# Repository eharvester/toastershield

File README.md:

# **toastershield**

An SMT reflow oven shield for the Arduino Uno.

## 1. Software
 
 The following steps were tested in Linux (Ubuntu).
 
### Set the following environment variables

`PATH_TO_ARDUINO_IDE = /path/to/your/arduinoIDE`

`ARDUINO_IDE_VER = 1.6.X`  (depending on your version)

`GITHUB_MIRROR = /path/to/your/github/mirror` (optional, local github mirror otherwise https://github.com is used per default)

### Connect Arduino Uno via USB cable

Make sure you have write permissions to `/dev/ttyUSB0` and execute the following commands:

`$make`

`$make upload`

If the shield is attached to the Arduino Uno board, you should hear a beep  and see something on the display.

## 2. Hardware

**_WARNING - DANGER - HIGH VOLTAGE - ELECTRIC SHOCK HAZARD - EXPERTS ONLY
(shield, heater, fan and transformer are connected to 120VAC)_**

### Parts List:

- toaster oven, to be converted (for use on 120VAC)
- Arduino Uno board
- toastershield PCB (see Eagle files and parts list)
- transformer PCB (see Eagle files and parts list)
- SH1106 OLED module
- 2 pushbuttons
- 1 LED,
- 2 wafer connectors (4 pin)
- some ribbon cable (to connect the OLED module and the switches+LED with wafer connectors)
- power cable with ground / 20 A
- power cable feedthrough coupler
- K-type thermocouple wire pair (about 50cm)
- some cable (AWG 16 for heater, AWG 24 for fan and 12VAC supply)
- 6.3mm crimp terminal spade connectors (female, insulated)
- ring tongue crimp terminals (for grounding)
- hardware for mounting boards and grounding
- fiberglass cloth (for thermal insulation)
- silicone glue

PCBs can be made with the [toner transfer method](http://www.instructables.com/id/Cheap-and-Easy-Toner-Transfer-for-PCB-Making) easily (single layer). All goes inside the oven (original buttons, switches, timers, bell aso. are stripped out). Make sure that there is sufficient air ventilation in order to keep the temperature around the boards and cables below 70C (a cooling fan might be necessary). Some thermal insulation on the outside of the oven compartment is necessary (treat fiberglass cloth with silicon glue on the cutting lines before cutting). Cut out an opening for the USB port, preferably on the front (so you can easily update the firmware and optionally monitor and control the oven from a computer).  Drill a hole into the oven compartment wall and feed the thermocouple wire pair through it and seal the hole with silicone glue later (after everything is working and tested). 

**_WARNING - DANGER - HIGH VOLTAGE - ELECTRIC SHOCK HAZARD - EXPERTS ONLY
(shield, heater, fan and transformer are connected to 120VAC)_**

## 3. To Do
- menu for adjusting temperature/time (at the moment fixed for PbSn solder) via pushbuttons
- interface for Processing
- Processing GUI  

***
## Pictures:

Picture 1: Assembled shield top.
***

Picture 2: Assembled shield bottom.
***

Picture 3: Modified power connection, plug replaced by screw terminals.
***

Picture 4: Wired shield sitting on Uno board.
***

Picture 5: Wired transformer board.
***

Picture 6: Complete wiring.
***

Picture 7: Wiring of front panel.
***

Pincture 8: Front panel.

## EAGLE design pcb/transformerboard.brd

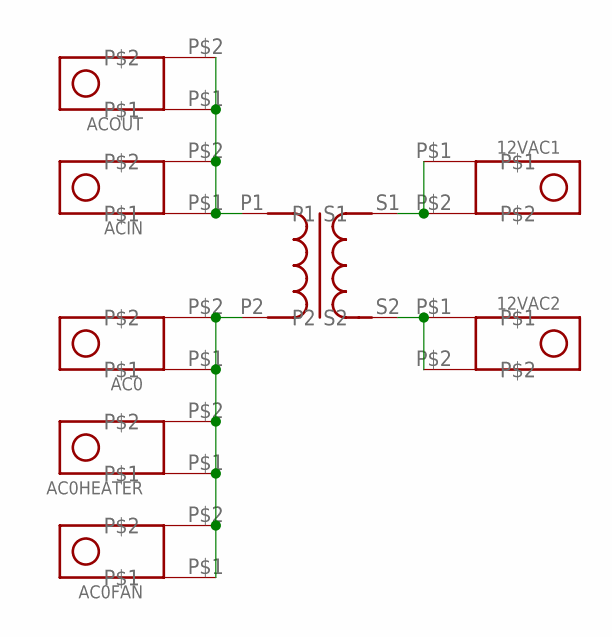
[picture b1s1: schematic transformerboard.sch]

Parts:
12VAC1, 12VAC2: QUICKCONNECT-TAB; QUICKCONNECT-TAB-6.35X0.81
AC0, AC0FAN, AC0HEATER: QUICKCONNECT-TAB; QUICKCONNECT-TAB-6.35X0.81
ACIN: QUICKCONNECT-TAB; QUICKCONNECT-TAB-6.35X0.81
ACOUT: QUICKCONNECT-TAB; QUICKCONNECT-TAB-6.35X0.81
T1: TRANSFORMER; 1.6X1.4.X1.3

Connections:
unnamed: ACIN.P$1, ACIN.P$2, ACOUT.P$1, ACOUT.P$2, T1.P1
unnamed: AC0.P$1, AC0.P$2, AC0FAN.P$1, AC0FAN.P$2, AC0HEATER.P$1, AC0HEATER.P$2, T1.P2
unnamed: 12VAC1.P$1, 12VAC1.P$2, T1.S1
unnamed: 12VAC2.P$1, 12VAC2.P$2, T1.S2

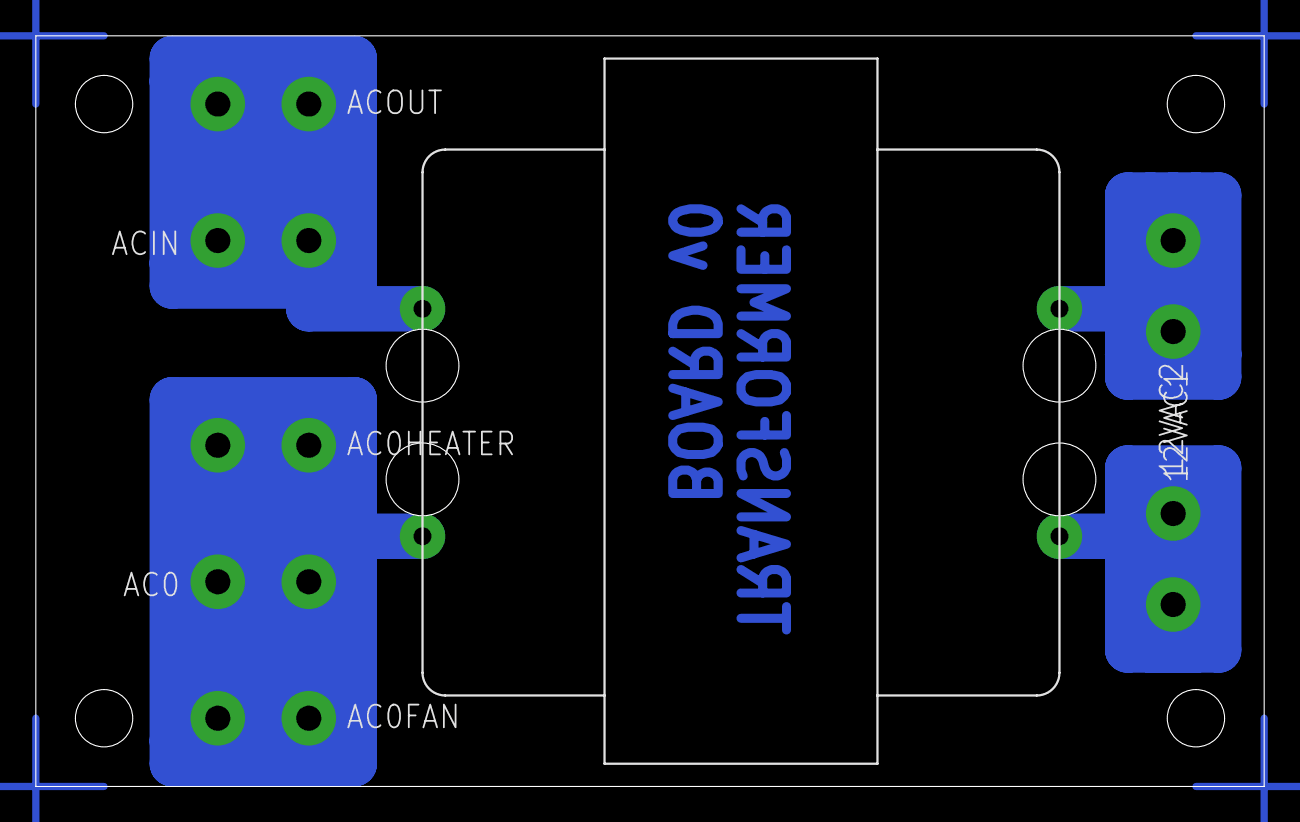
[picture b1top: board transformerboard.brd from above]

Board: 2 copper layers, 68.6 x 41.9 mm, 8 parts (0 on the bottom side), 4 nets.

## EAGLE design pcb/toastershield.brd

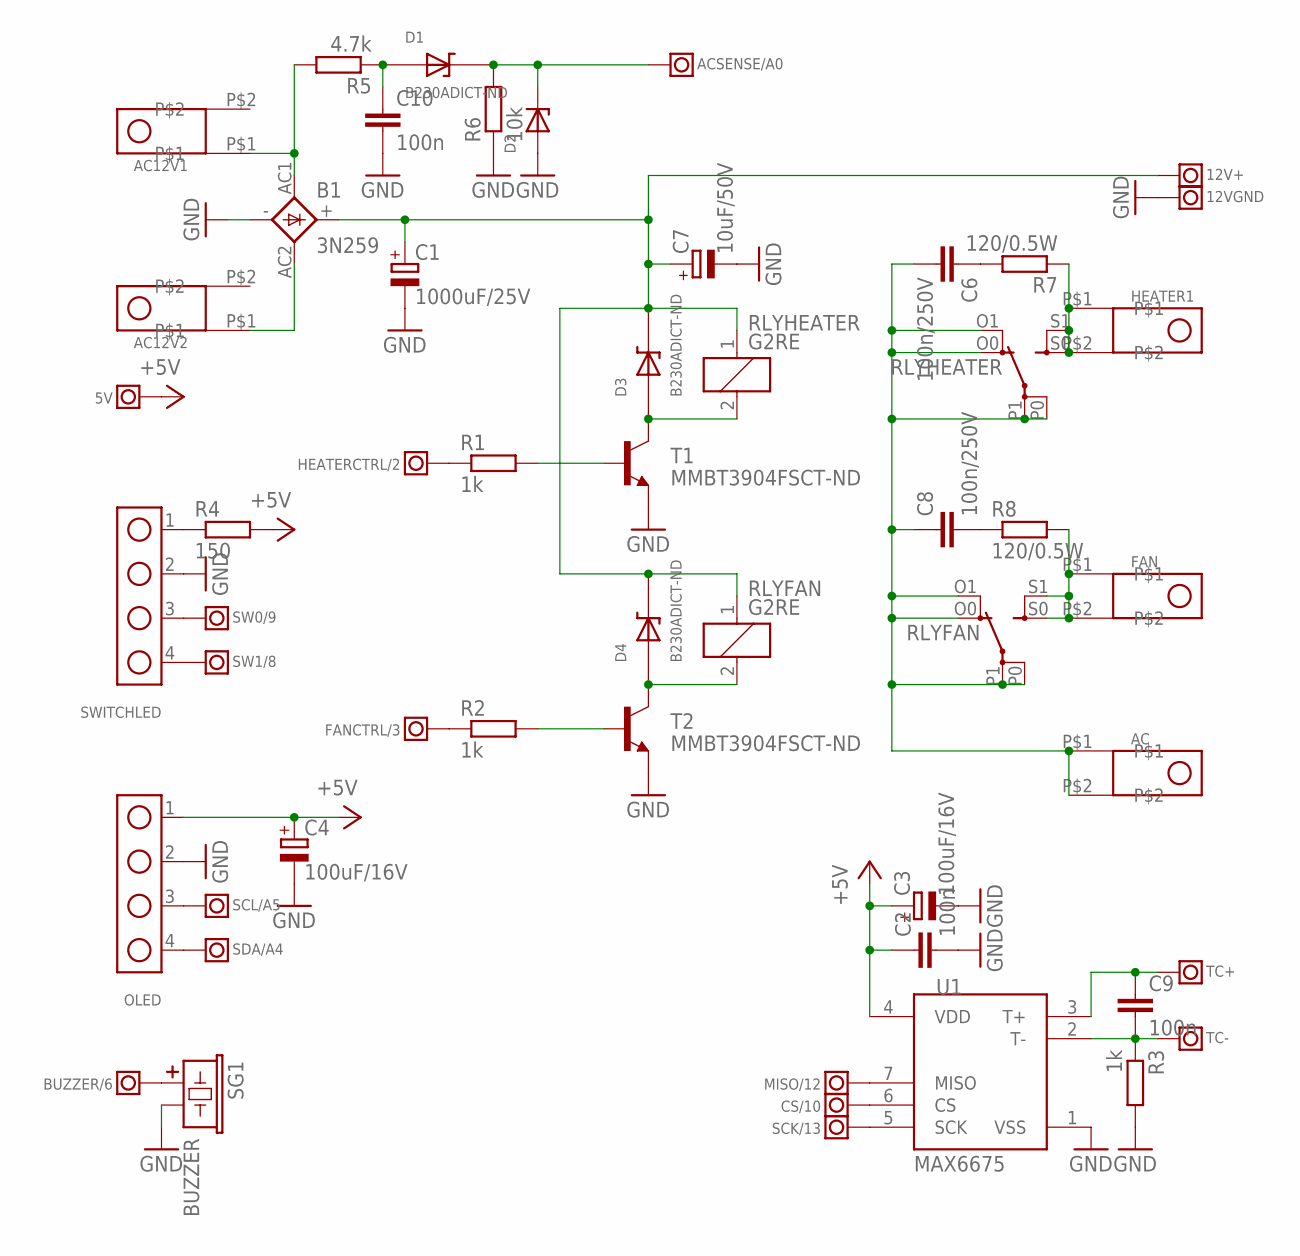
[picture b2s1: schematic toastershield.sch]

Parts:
5V, 12V+, 12VGND: PIN-HEADER; PIN-HEADER-MALE
AC, AC12V1, AC12V2: QUICKCONNECT-TAB; QUICKCONNECT-TAB-6.35X0.81
ACSENSE/A0: PIN-HEADER; PIN-HEADER-MALE
B1: 3N259; KBPM
BUZZER/6: PIN-HEADER; PIN-HEADER-MALE
C1: 1000uF/25V; E5-13
C2, C9, C10: 100n; C0603
C3, C4: 100uF/16V; E2,5-7
C6, C8: 100n/250V; C1210
C7: 10uF/50V; E2,5-5
CS/10: PIN-HEADER; PIN-HEADER-MALE
D1, D3, D4: B230ADICT-ND; SMA/SMB
D2: MA8051CT; SOD323-W
FAN: QUICKCONNECT-TAB; QUICKCONNECT-TAB-6.35X0.81
FANCTRL/3: PIN-HEADER; PIN-HEADER-MALE
HEATER1: QUICKCONNECT-TAB; QUICKCONNECT-TAB-6.35X0.81
HEATERCTRL/2: PIN-HEADER; PIN-HEADER-MALE
MISO/12: PIN-HEADER; PIN-HEADER-MALE
OLED: 4-PIN-WAFER-CONN; WAFER_MALE_4PIN
R1, R2, R3: 1k; R0603
R4: 150; R0603
R5: 4.7k; R0603
R6: 10k; R0603
R7, R8: 120/0.5W; R1210
RLYFAN: G2RE
RLYHEATER: G2RE
SCK/13: PIN-HEADER; PIN-HEADER-MALE
SCL/A5: PIN-HEADER; PIN-HEADER-MALE
SDA/A4: PIN-HEADER; PIN-HEADER-MALE
SG1: BUZZER; BUZZER-12X7.5
SW0/9, SW1/8: PIN-HEADER; PIN-HEADER-MALE
SWITCHLED: 4-PIN-WAFER-CONN; WAFER_MALE_4PIN
T1, T2: MMBT3904FSCT-ND; SOT-23
TC+: PIN-HEADER; PIN-HEADER-MALE
TC-: PIN-HEADER; PIN-HEADER-MALE
U1: MAX6675; SO08-MAX6675

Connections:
12VDC: 12V+.P$1, B1.+, C1.+, C7.+, D3.1 (CAT), D4.1 (CAT), RLYFAN.1, RLYHEATER.1
+5V: 5V.P$1, C2.1, C3.+, C4.+, OLED.1, R4.2, U1.4 (VDD)
AC: AC.P$1, AC.P$2, C6.2, C8.1, RLYFAN.O0 (O), RLYFAN.O1 (O), RLYFAN.P0, RLYFAN.P1, RLYHEATER.O0 (O), RLYHEATER.O1 (O), RLYHEATER.P0, RLYHEATER.P1
AC12V0: AC12V1.P$1, B1.AC1, R5.2
AC12V1: AC12V2.P$1, B1.AC2
BUZZER: BUZZER/6.P$1, SG1.+ (1)
FAN: FAN.P$1, FAN.P$2, R8.2, RLYFAN.S0 (S), RLYFAN.S1 (S)
GND: 12VGND.P$1, B1.-, C1.-, C2.2, C3.-, C4.-, C7.-, C10.2, D2.A (AN), OLED.2, R3.2, R6.1, SG1.- (2), SWITCHLED.2, T1.2 (E), T2.2 (E), U1.1 (VSS)
HEATER: HEATER1.P$1, HEATER1.P$2, R7.1, RLYHEATER.S0 (S), RLYHEATER.S1 (S)
LED+: R4.1, SWITCHLED.1
unnamed: C9.1, TC+.P$1, U1.3 (T+)
unnamed: FANCTRL/3.P$1, R2.1
unnamed: HEATERCTRL/2.P$1, R1.1
unnamed: D3.2 (AN), RLYHEATER.2, T1.3 (C)
unnamed: D4.2 (AN), RLYFAN.2, T2.3 (C)
unnamed: R1.2, T1.1 (B)
unnamed: R2.2, T2.1 (B)
unnamed: MISO/12.P$1, U1.7 (MISO)
unnamed: C9.2, R3.1, TC-.P$1, U1.2 (T-)
unnamed: CS/10.P$1, U1.6 (CS)
unnamed: SCK/13.P$1, U1.5 (SCK)
unnamed: SW0/9.P$1, SWITCHLED.3
unnamed: SW1/8.P$1, SWITCHLED.4
unnamed: OLED.3, SCL/A5.P$1
unnamed: OLED.4, SDA/A4.P$1
unnamed: C10.1, D1.2 (AN), R5.1
unnamed: ACSENSE/A0.P$1, D1.1 (CAT), D2.C (CAT), R6.2
unnamed: C8.2, R8.1
unnamed: C6.1, R7.2

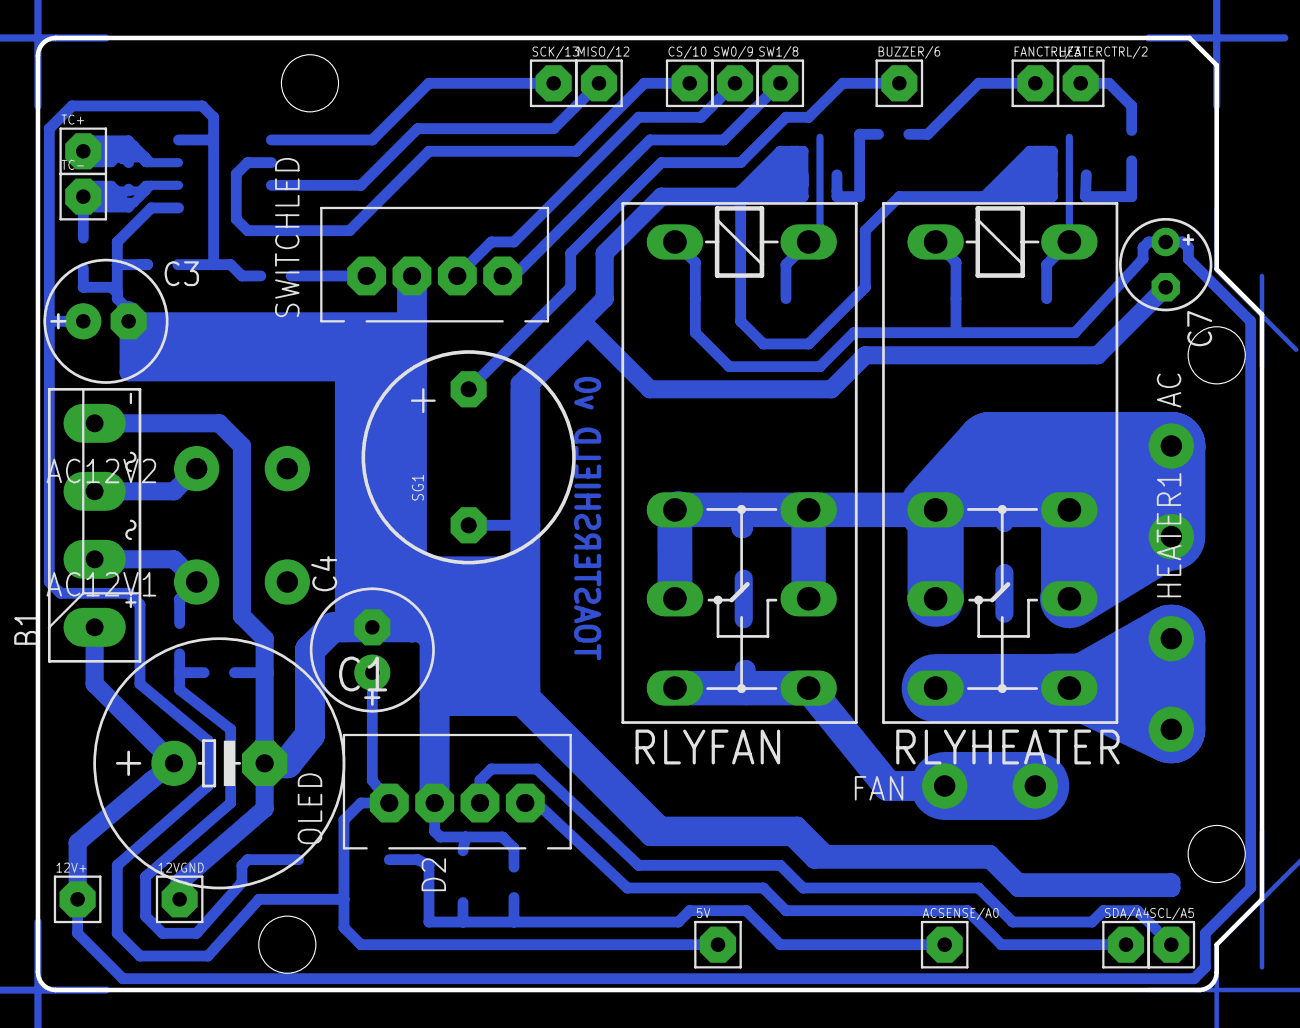
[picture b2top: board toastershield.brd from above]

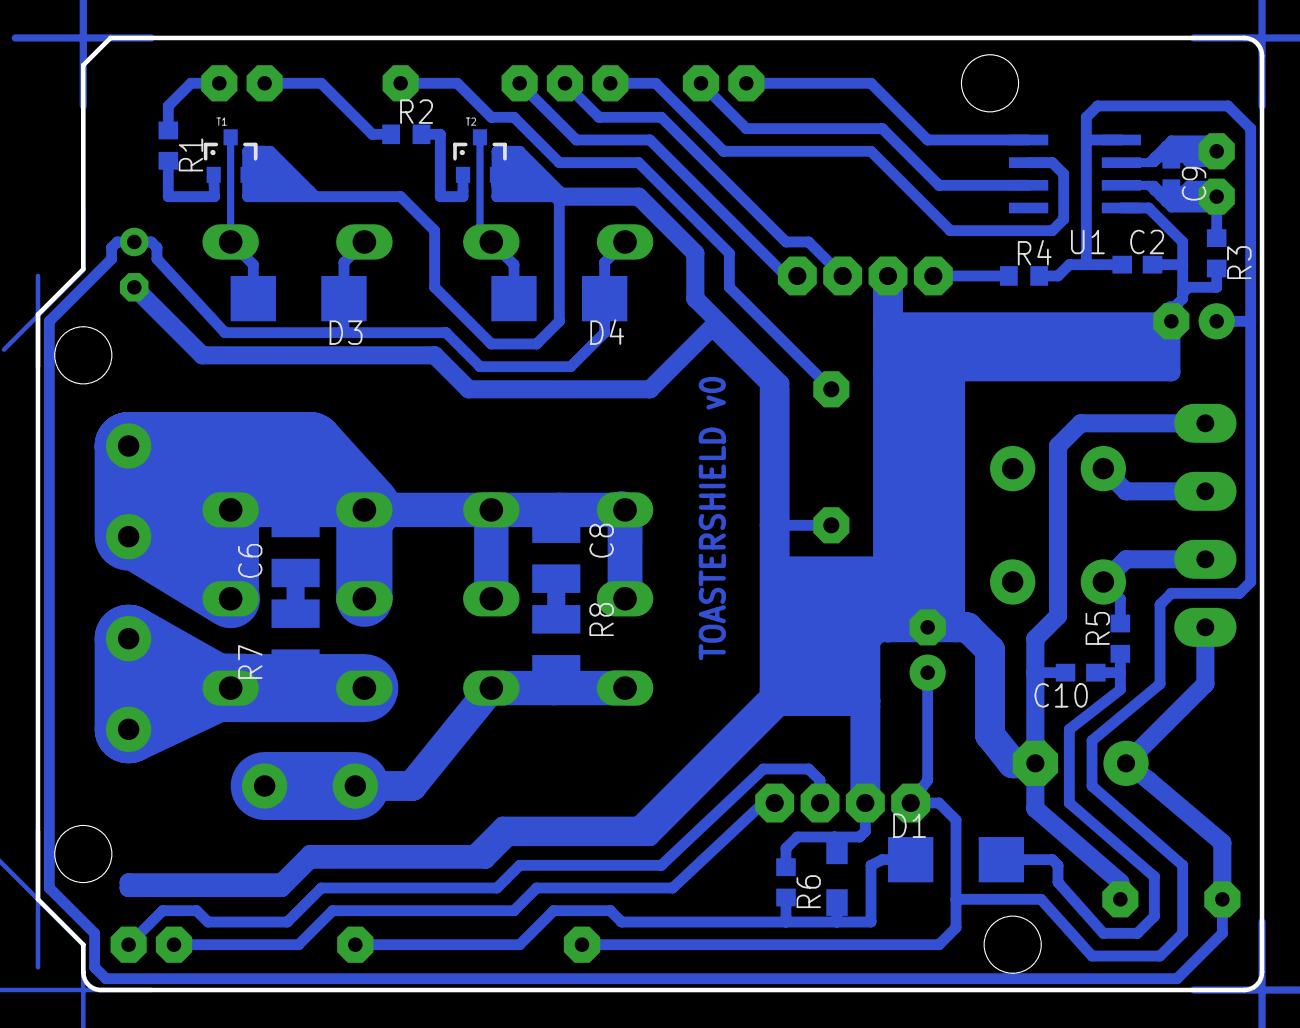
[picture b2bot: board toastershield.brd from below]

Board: 2 copper layers, 68.6 x 53.3 mm, 51 parts (19 on the bottom side), 29 nets.

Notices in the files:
parts and their libraries:
SparkFun-AnalogIC: Licensing:Creative Commons ShareAlike 4.0 International - https://creativecommons.org/licenses/by-sa/4.0
